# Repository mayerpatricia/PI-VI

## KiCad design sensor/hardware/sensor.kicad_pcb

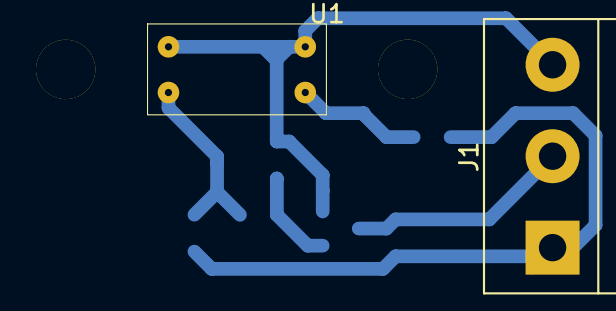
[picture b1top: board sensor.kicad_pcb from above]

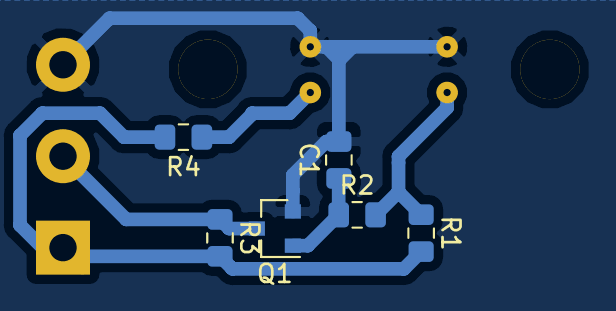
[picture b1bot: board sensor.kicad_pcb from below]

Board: 2 copper layers, 8 parts (6 on the bottom side), 6 nets.

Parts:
C1: 100n; C_0805_2012Metric_Pad1.15x1.40mm_HandSolder
J1: conector; TerminalBlock_bornier-3_P5.08mm
Q1: Q_NPN_BEC; SOT-23
R1, R3: 1k; R_0805_2012Metric_Pad1.15x1.40mm_HandSolder
R2: 100R; R_0805_2012Metric_Pad1.15x1.40mm_HandSolder
R4: 220R; R_0805_2012Metric_Pad1.15x1.40mm_HandSolder
U1: 4N35; sensor_phct203

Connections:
+5V: J1.1, R1.2, R3.2, R4.2
GND: C1.2, J1.3, Q1.2, U1.2, U1.4
unnamed: C1.1, Q1.1, R2.1
unnamed: J1.2, Q1.3, R3.1
unnamed: R1.1, R2.2, U1.5
unnamed: R4.1, U1.1

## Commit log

2019-03-26 placa para o sensor optico
2019-03-26 simulação do sensor optico
2019-03-26 atualizado
